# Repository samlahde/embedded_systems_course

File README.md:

# embedded_systems_course
Robotic car for embedded systems project course

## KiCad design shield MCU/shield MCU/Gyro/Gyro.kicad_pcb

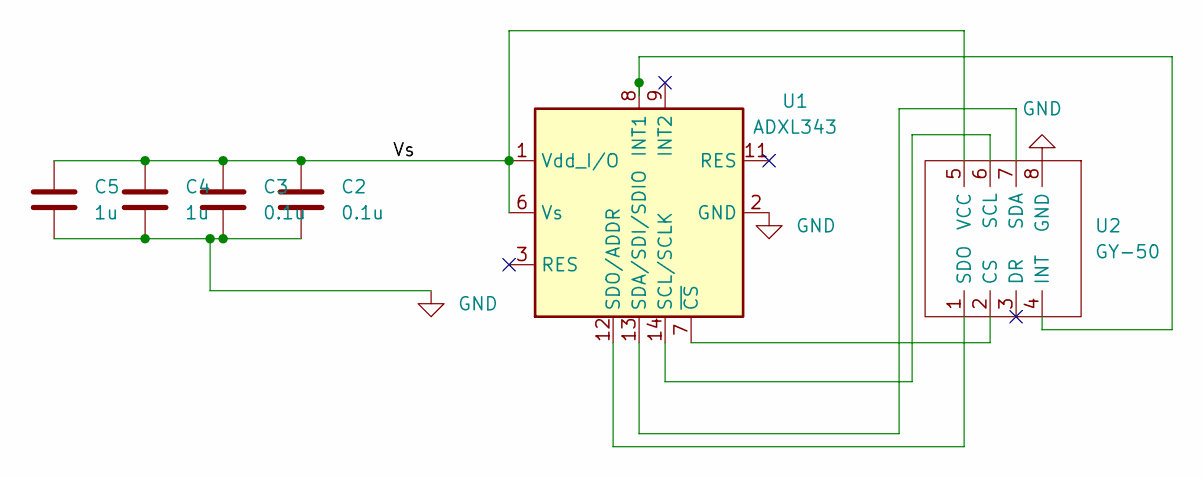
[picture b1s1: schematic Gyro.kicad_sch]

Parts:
C2, C3: 0.1u; C_1206_3216Metric
C4, C5: 1u; C_1206_3216Metric
U1: ADXL343; LGA-14_3x5mm_P0.8mm_LayoutBorder1x6y
U2: GY-50

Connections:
/Vs: C2.1, C3.1, C4.1, C5.1, U1.1 (Vdd_I/O), U1.6 (Vs), U2.5 (VCC)
GND: C2.2, C3.2, C4.2, C5.2, U1.2 (GND), U1.4 (GND), U1.5 (GND), U2.8 (GND)
unnamed: U1.7 (~CS), U2.2 (CS)
unnamed: U1.8 (INT1), U2.4 (INT)
unnamed: U1.12 (SDO/ADDR), U2.1 (SDO)
unnamed: U1.13 (SDA/SDI/SDIO), U2.7 (SDA)
unnamed: U1.14 (SCL/SCLK), U2.6 (SCL)

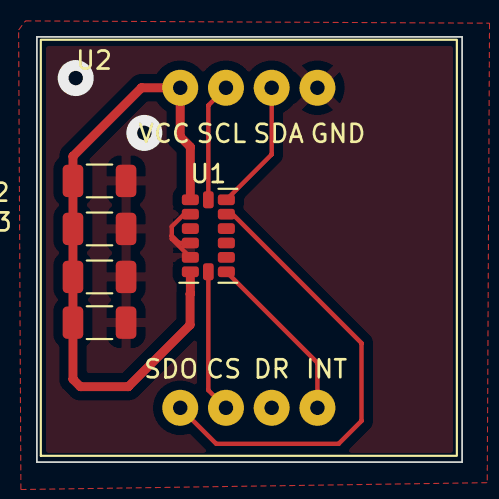
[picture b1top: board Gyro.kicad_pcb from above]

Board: 2 copper layers, 23.6 x 23.6 mm, 6 parts (0 on the bottom side), 7 nets.

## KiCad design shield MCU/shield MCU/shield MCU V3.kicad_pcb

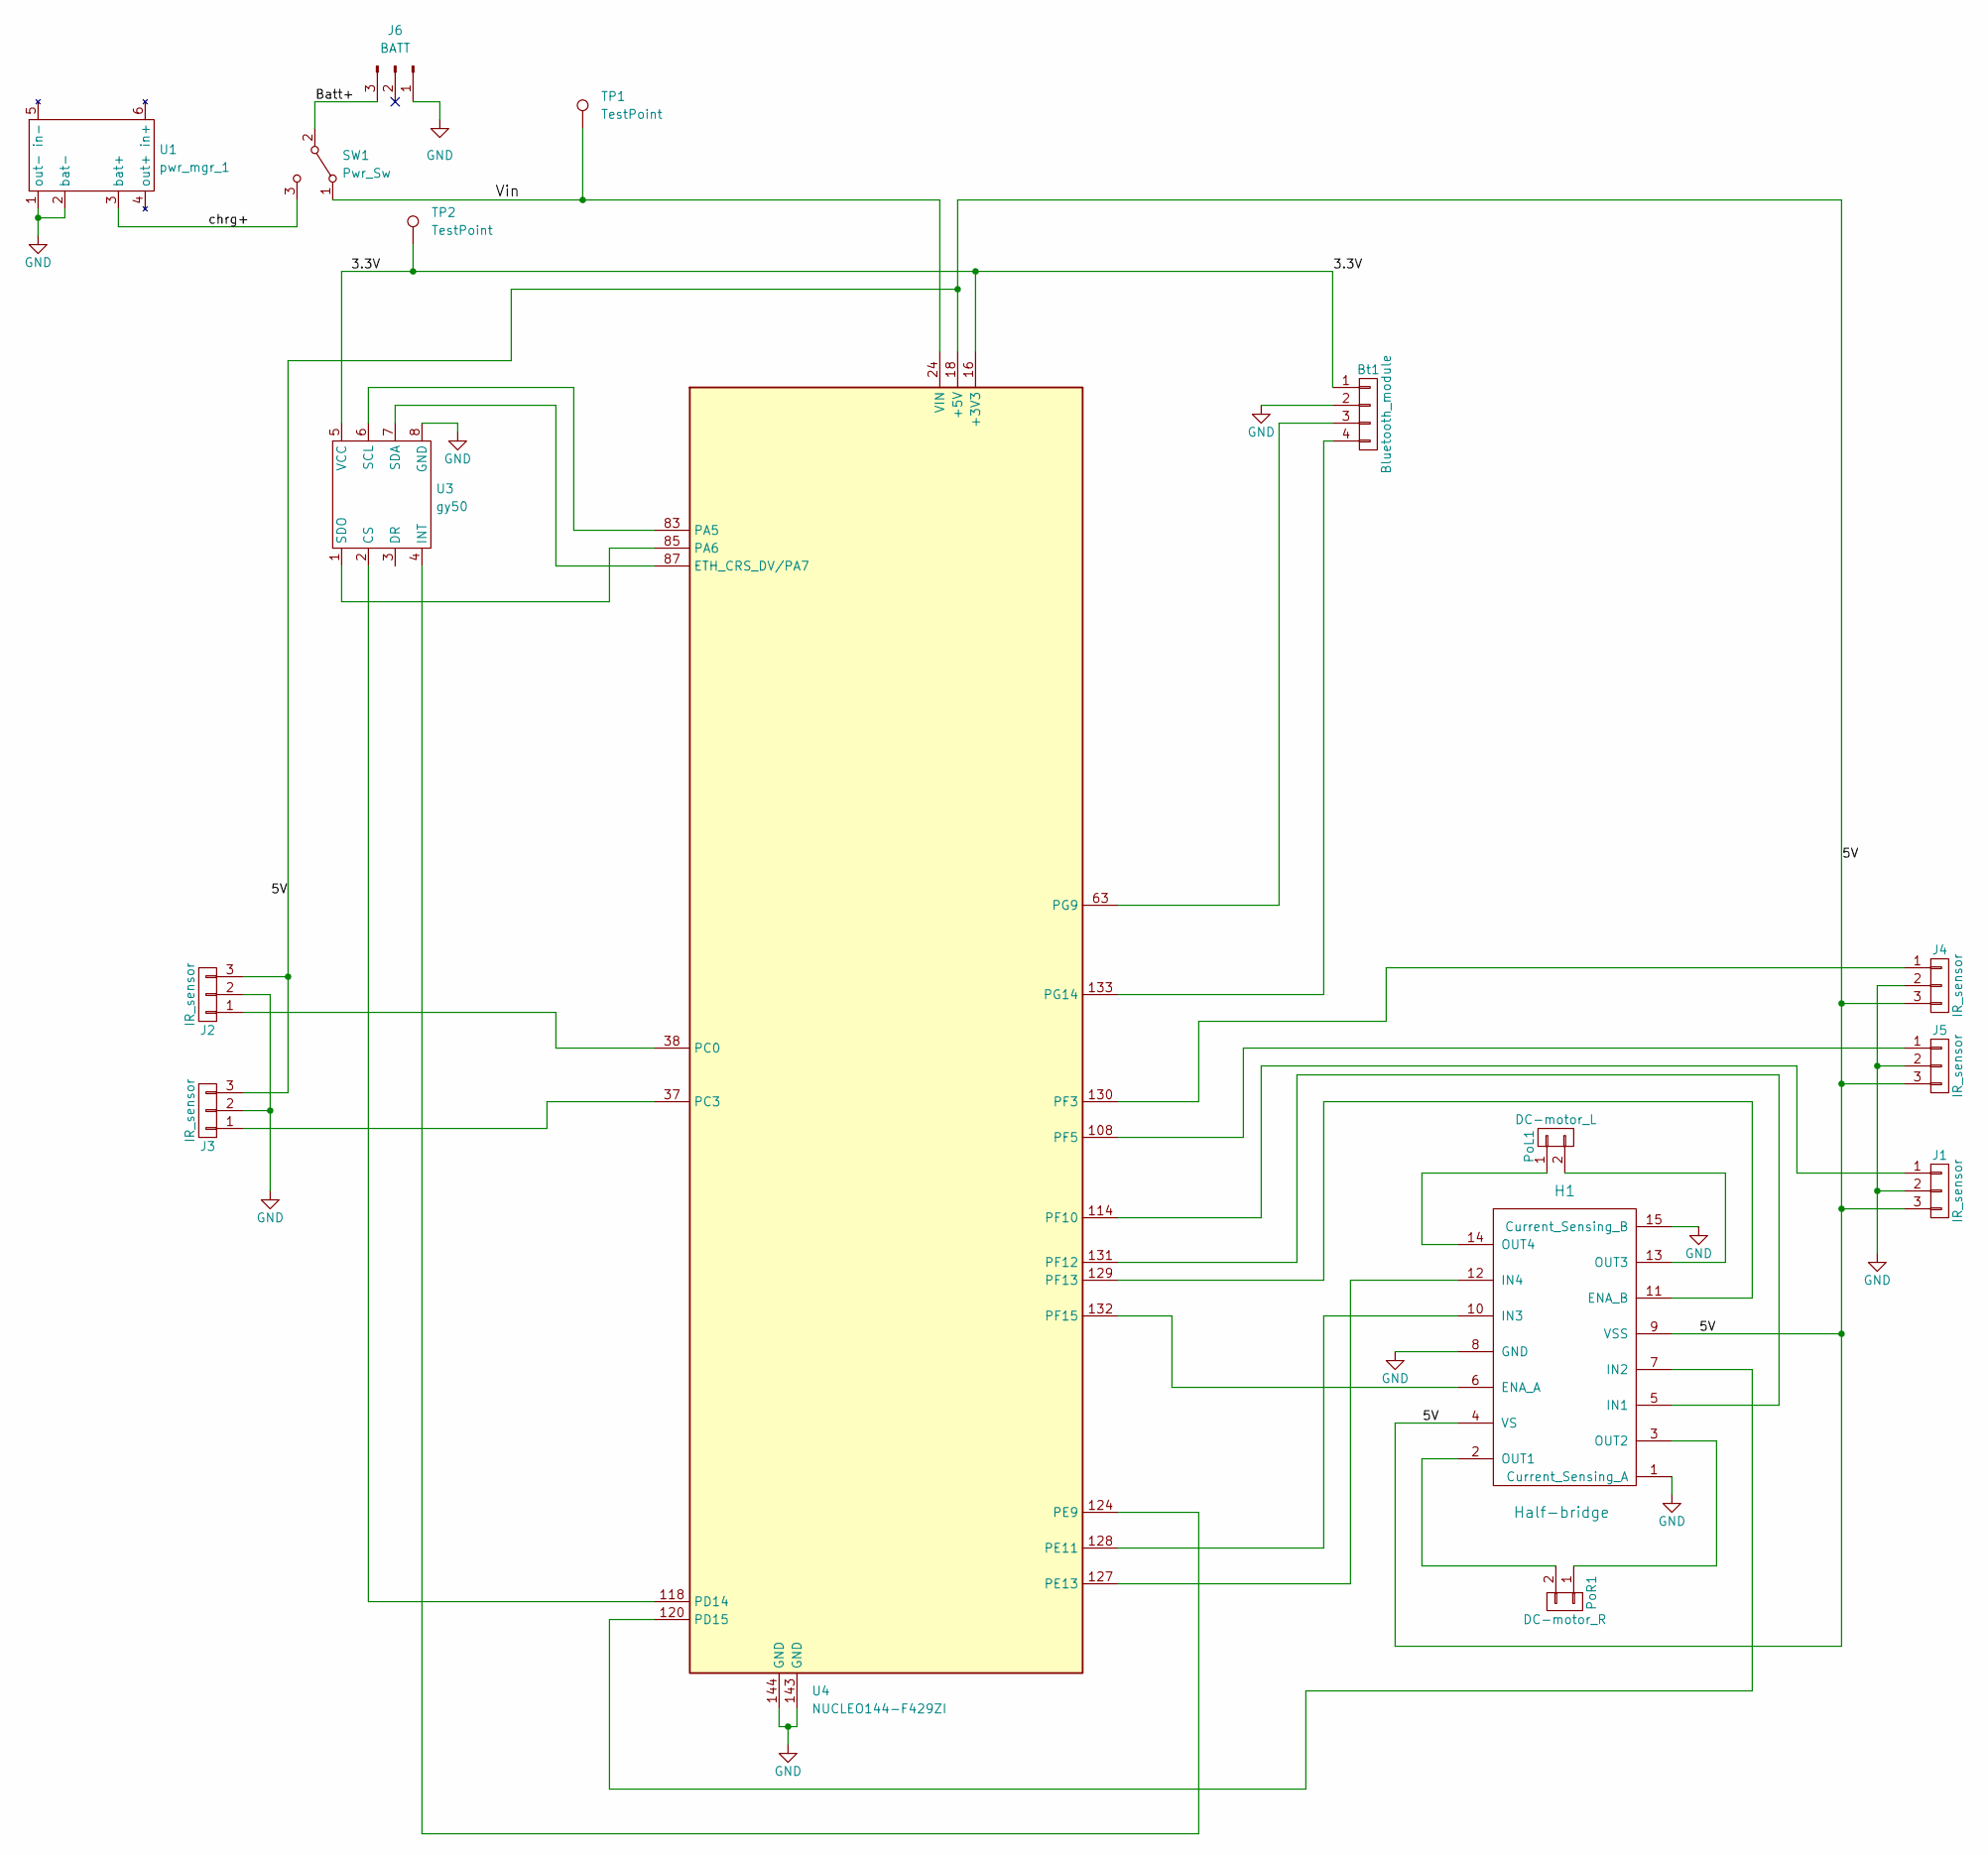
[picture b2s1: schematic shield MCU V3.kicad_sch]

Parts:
Bt1: Bluetooth_module; PinHeader_1x04_P2.54mm_Vertical
H1: Half-bridge; L298HN
J1, J2, J3, J4, J5: IR_sensor; PinHeader_1x03_P2.54mm_Vertical
J6: BATT; Connector_3pin
PoL1: DC-motor_L; PinHeader_1x02_P2.54mm_Horizontal
PoR1: DC-motor_R; PinHeader_1x02_P2.54mm_Horizontal
SW1: Pwr_Sw; SPDT
TP1, TP2: TestPoint; Pin_D0.7mm_L6.5mm_W1.8mm_FlatFork
U1: pwr_mgr_1; TPS4056
U3: gy50; GY-50
U4: NUCLEO144-F429ZI; ST_Morpho_Connector_144_STLink_MountingHoles_modded

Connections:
/3.3V: Bt1.1, TP2.1, U3.5 (VCC), U4.16 (+3V3)
/5V: H1.4 (VS), H1.9 (VSS), J1.3, J2.3, J3.3, J4.3, J5.3, U4.18 (+5V)
/Batt+: J6.3, SW1.2 (B)
/Vin: SW1.1 (A), TP1.1, U4.24 (VIN)
/chrg+: SW1.3 (C), U1.3 (bat+)
GND: Bt1.2, H1.1 (Current_Sensing_A), H1.8 (GND), H1.15 (Current_Sensing_B), J1.2, J2.2, J3.2, J4.2, J5.2, J6.1, U1.1 (out-), U1.2 (bat-), U3.8 (GND), U4.143 (GND), U4.144 (GND)
unnamed: Bt1.3, U4.63 (PG9)
unnamed: Bt1.4, U4.133 (PG14)
unnamed: H1.2 (OUT1), PoR1.2
unnamed: H1.3 (OUT2), PoR1.1
unnamed: H1.5 (IN1), U4.131 (PF12)
unnamed: H1.6 (ENA_A), U4.132 (PF15)
unnamed: H1.7 (IN2), U4.120 (PD15)
unnamed: H1.10 (IN3), U4.128 (PE11)
unnamed: H1.11 (ENA_B), U4.129 (PF13)
unnamed: H1.12 (IN4), U4.127 (PE13)
unnamed: H1.13 (OUT3), PoL1.2
unnamed: H1.14 (OUT4), PoL1.1
unnamed: J1.1, U4.114 (PF10)
unnamed: J2.1, U4.38 (PC0)
unnamed: J3.1, U4.37 (PC3)
unnamed: J4.1, U4.130 (PF3)
unnamed: J5.1, U4.108 (PF5)
unnamed: U3.1 (SDO), U4.85 (PA6)
unnamed: U3.2 (CS), U4.118 (PD14)
unnamed: U3.4 (INT), U4.124 (PE9)
unnamed: U3.6 (SCL), U4.83 (PA5)
unnamed: U3.7 (SDA), U4.87 (ETH_CRS_DV/PA7)

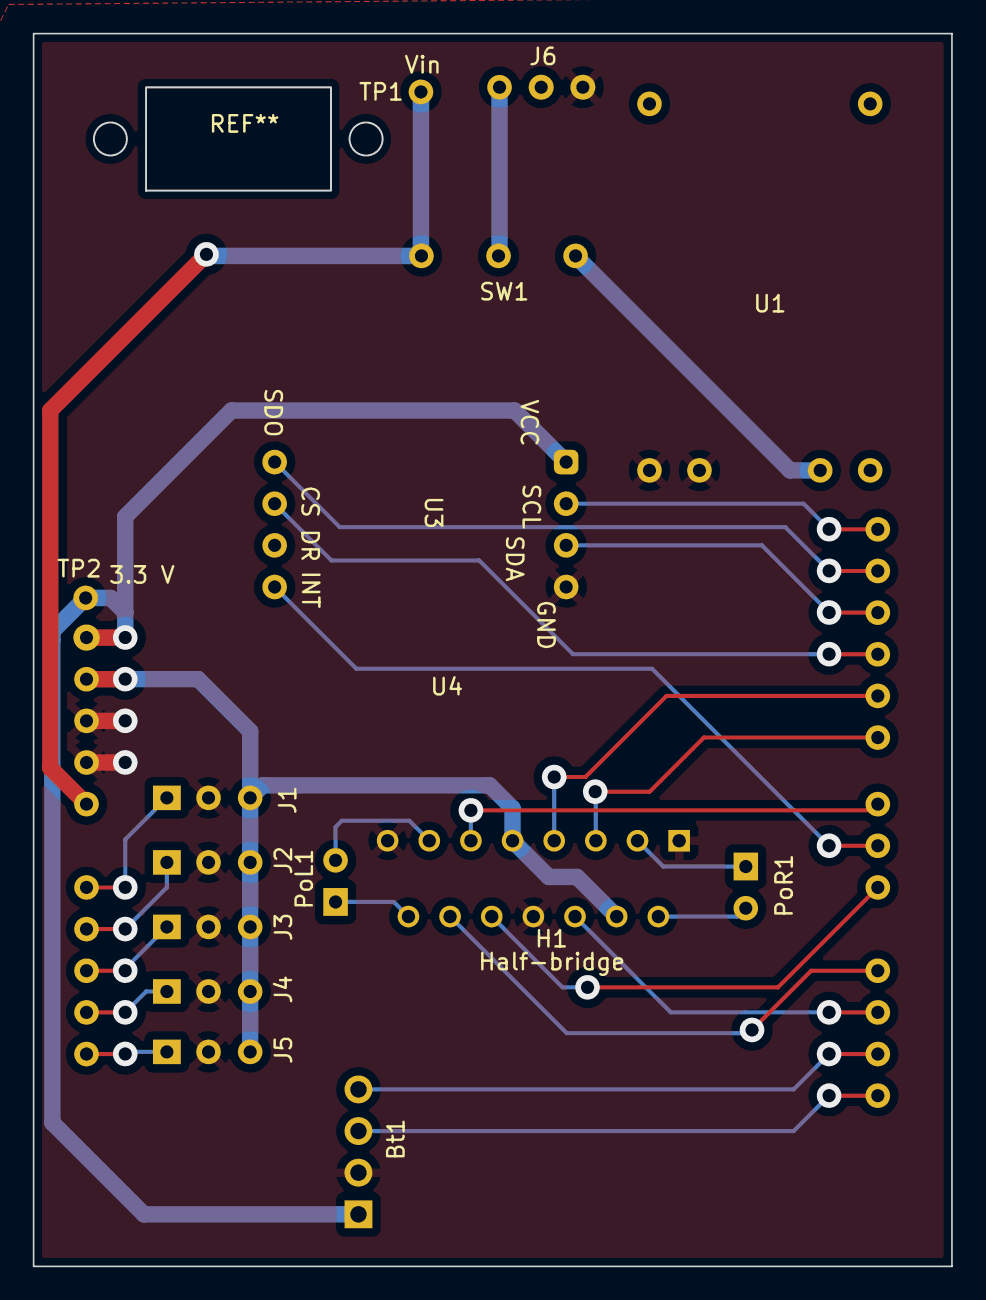
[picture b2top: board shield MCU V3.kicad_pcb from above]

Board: 2 copper layers, 56.0 x 75.2 mm, 16 parts (0 on the bottom side), 28 nets.

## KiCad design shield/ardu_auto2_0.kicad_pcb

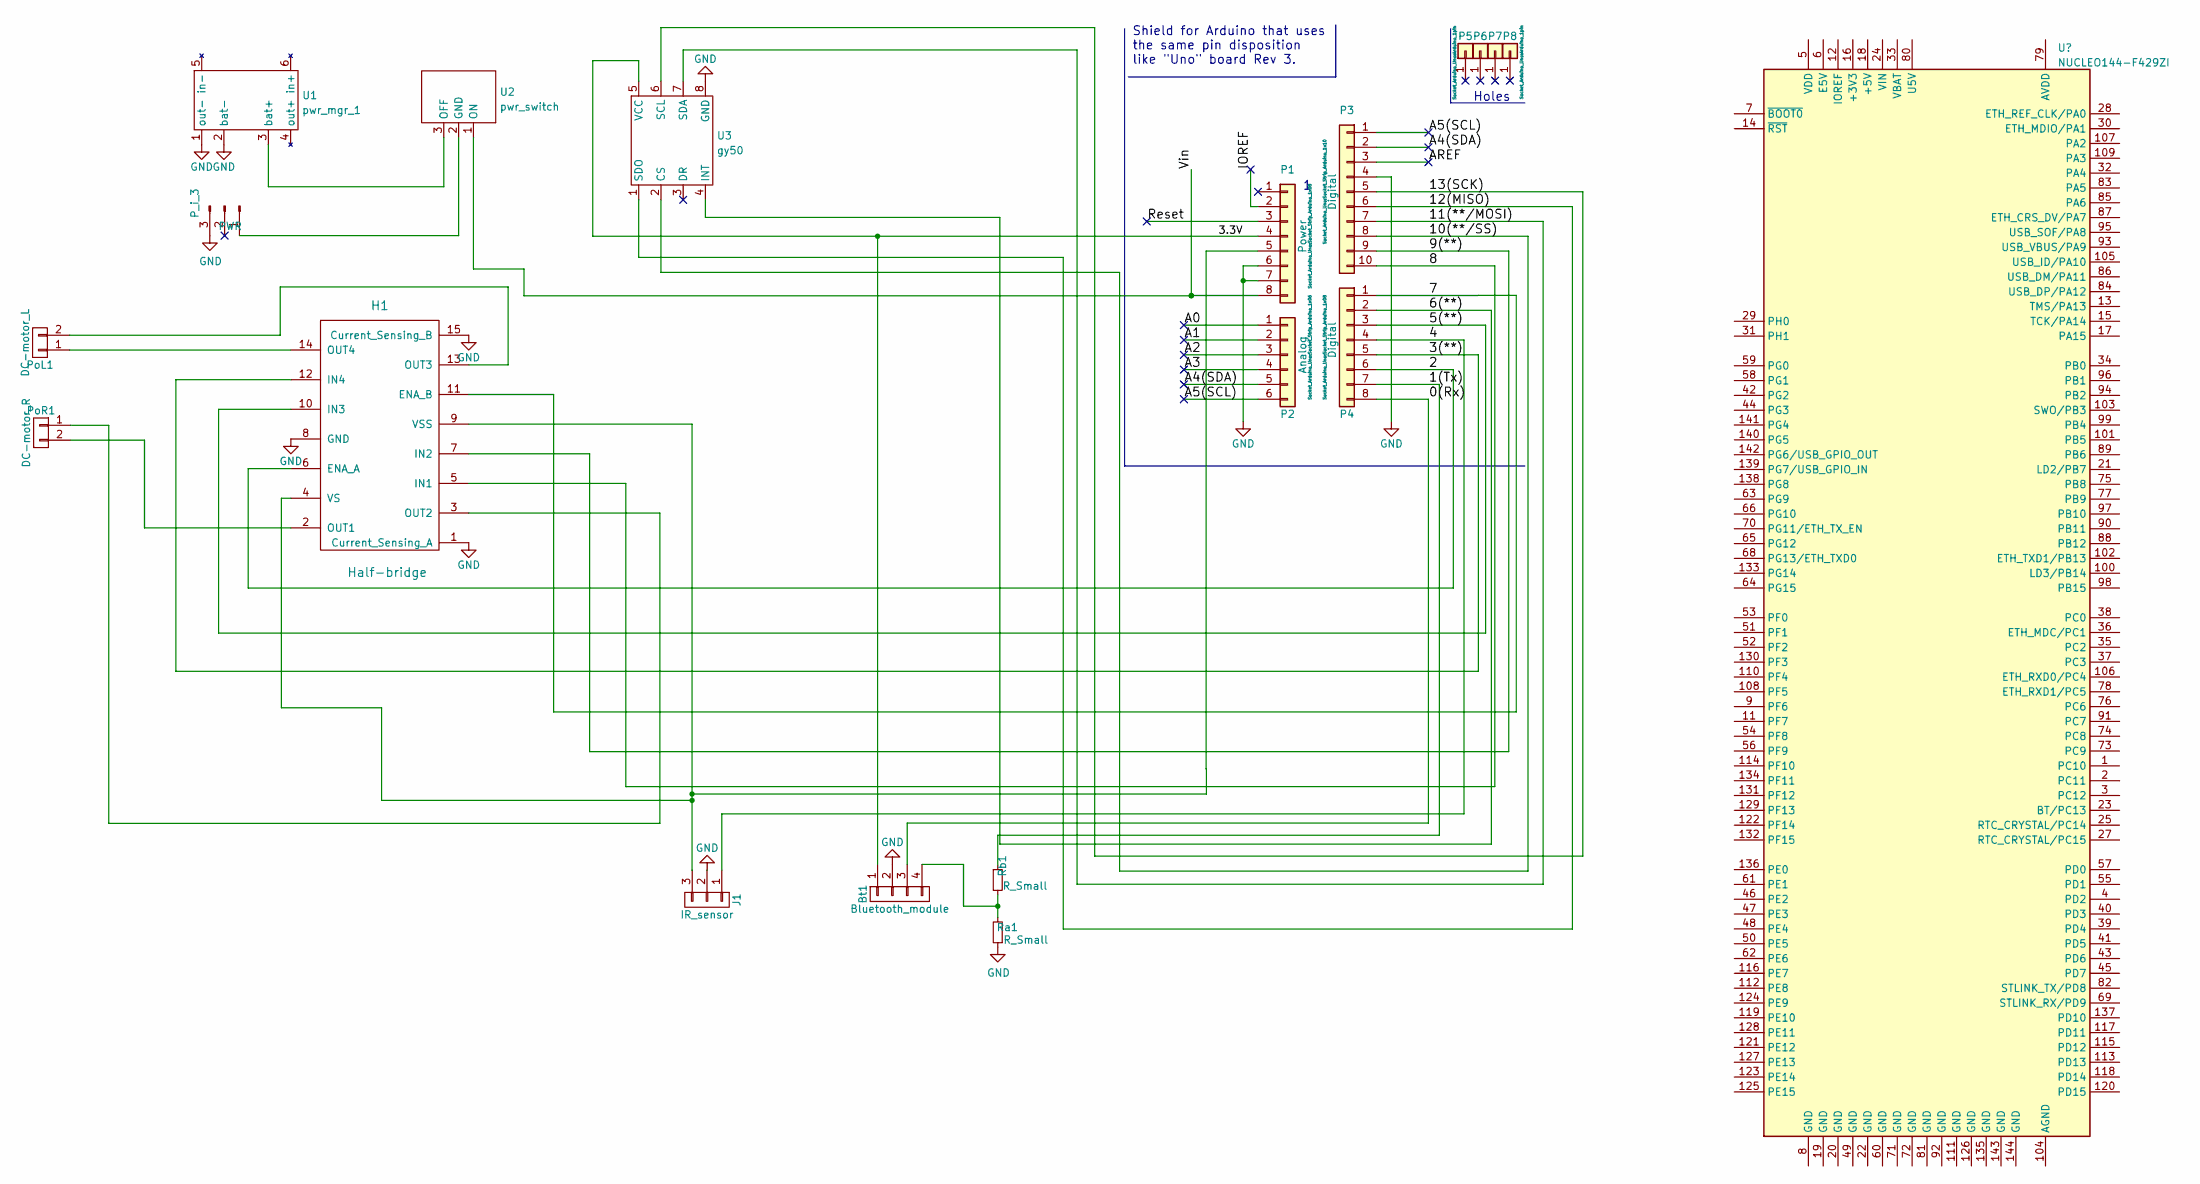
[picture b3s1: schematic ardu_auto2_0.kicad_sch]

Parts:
Bt1: Bluetooth_module; PinHeader_1x04_P2.54mm_Vertical
H1: Half-bridge
J1: IR_sensor; PinHeader_1x03_P2.54mm_Vertical
P1: Power; Socket_Strip_Arduino_1x08
P2: Analog; Socket_Strip_Arduino_1x06
P3: Digital; Socket_Strip_Arduino_1x10
P4: Digital; Socket_Strip_Arduino_1x08
P5, P6, P7, P8: CONN_01X01; Arduino_1pin
P_i_3: PWR; PinHeader_1x03_P2.54mm_Horizontal
PoL1: DC-motor_L; PinHeader_1x02_P2.54mm_Horizontal
PoR1: DC-motor_R; PinHeader_1x02_P2.54mm_Horizontal
Ra1: R_Small; PinHeader_1x02_P2.54mm_Horizontal
Rb1: R_Small; PinHeader_1x02_P2.54mm_Horizontal
U1: pwr_mgr_1; pwr_mfr_1
U2: pwr_switch; pwr_stw
U3: gy50

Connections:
/0(Rx): Bt1.3, P4.8
/1(Tx): P4.7, Rb1.1
/2: H1.6 (ENA_A), P4.6
/3(**): H1.12 (IN4), P4.5
/3.3V: Bt1.1, P1.4, U3.5 (VCC)
/4: J1.1, P4.4
/5(**): H1.10 (IN3), P4.3
/6(**): P4.2, U3.4 (INT)
/7: H1.11 (ENA_B), P4.1
/8: H1.5 (IN1), P3.10
/9(**): H1.7 (IN2), P3.9
/10(**/SS): P3.8, U3.2 (CS)
/11(**/MOSI): P3.7, U3.7 (SDA)
/12(MISO): P3.6, U3.1 (SDO)
/13(SCK): P3.5, U3.6 (SCL)
/A0: P2.1
/A1: P2.2
/A2: P2.3
/A3: P2.4
/A4(SDA): P2.5, P3.2
/A5(SCL): P2.6, P3.1
/AREF: P3.3
/IOREF: P1.2
/Reset: P1.3
/Vin: P1.8, U2.1 (ON)
GND: Bt1.2, H1.1 (Current_Sensing_A), H1.8 (GND), H1.15 (Current_Sensing_B), J1.2, P1.6, P1.7, P3.4, P_i_3.3, Ra1.1, U1.1 (out-), U1.2 (bat-), U3.8 (GND)
unnamed: Bt1.4, Ra1.2, Rb1.2
unnamed: H1.2 (OUT1), PoR1.2
unnamed: H1.3 (OUT2), PoR1.1
unnamed: H1.13 (OUT3), PoL1.2
unnamed: H1.14 (OUT4), PoL1.1
unnamed: H1.4 (VS), H1.9 (VSS), J1.3, P1.5
unnamed: P_i_3.1, U2.2 (GND)
unnamed: U1.3 (bat+), U2.3 (OFF)

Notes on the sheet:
Shield for Arduino that uses the same pin disposition like "Uno" board Rev 3.
Holes

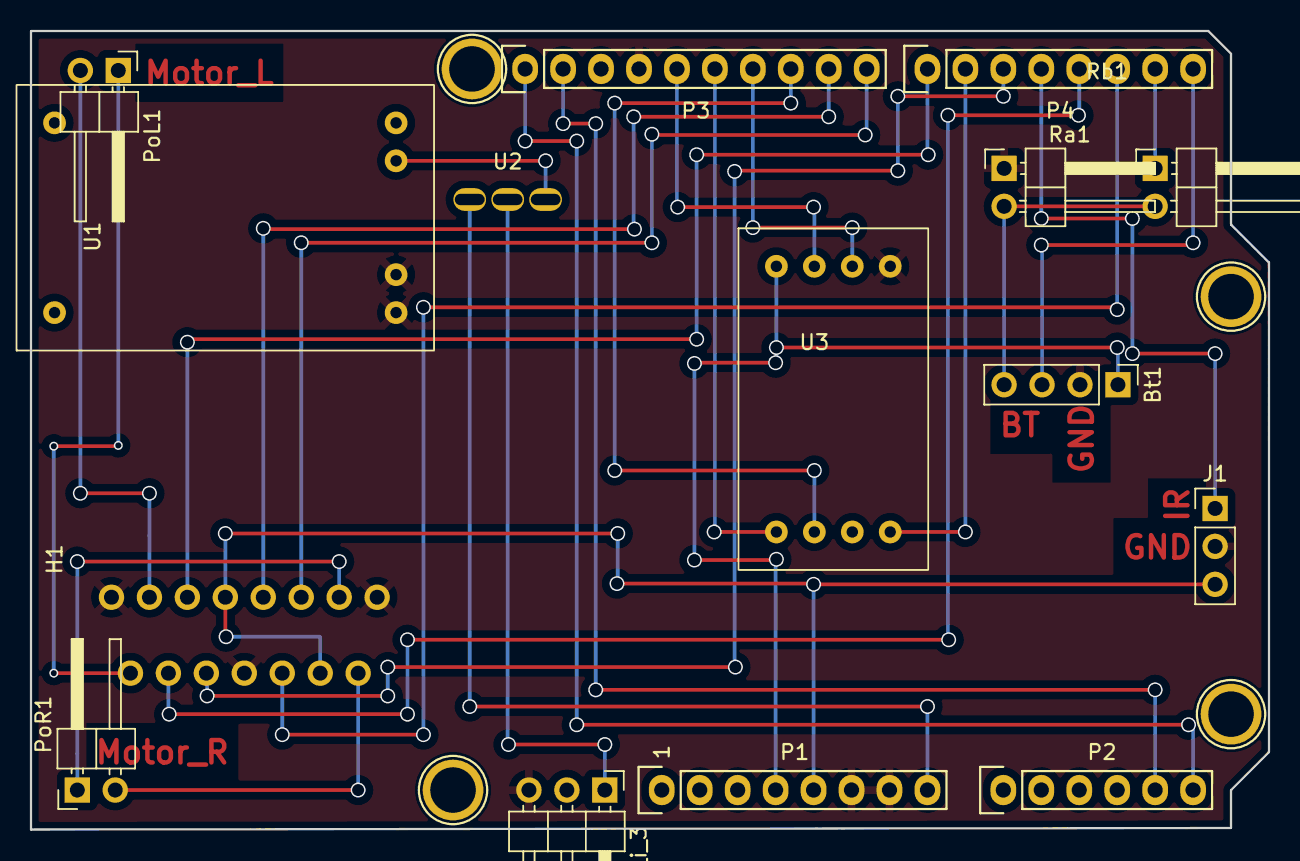
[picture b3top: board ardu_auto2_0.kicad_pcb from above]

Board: 2 copper layers, 82.9 x 53.4 mm, 19 parts (0 on the bottom side), 27 nets.

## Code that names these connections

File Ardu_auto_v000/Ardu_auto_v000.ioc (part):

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Mcu.Name=STM32F429ZITx
Mcu.Package=LQFP144
Mcu.UserName=STM32F429ZITx
PA13.Mode=Trace_Asynchronous_SW
PA13.Signal=SYS_JTMS-SWDIO
PA14.Mode=Trace_Asynchronous_SW
PA14.Signal=SYS_JTCK-SWCLK
PA2.Mode=Asynchronous
PA2.Signal=USART2_TX
PA3.Mode=Asynchronous
PA3.Signal=USART2_RX
PA5.GPIOParameters=GPIO_Label
PA5.GPIO_Label=SCK
PA5.Mode=Full_Duplex_Master
PA5.Signal=SPI1_SCK
PA6.GPIOParameters=GPIO_Label
PA6.GPIO_Label=SDO
PA6.Mode=Full_Duplex_Master
PA6.Signal=SPI1_MISO
PA7.GPIOParameters=GPIO_Label
PA7.GPIO_Label=SDA
PA7.Mode=Full_Duplex_Master
PA7.Signal=SPI1_MOSI
PB3.Mode=Trace_Asynchronous_SW
PB3.Signal=SYS_JTDO-SWO
PB8.Signal=I2C1_SCL
PB9.Signal=I2C1_SDA
PC0.GPIOParameters=GPIO_Label
PC0.GPIO_Label=IR5
PC0.Signal=ADCx_IN10
PC3.GPIOParameters=GPIO_Label
PC3.GPIO_Label=IR4
PC3.Signal=ADCx_IN13
PD14.GPIOParameters=PinState,GPIO_PuPd,GPIO_Label
PD14.GPIO_Label=SPI_CS
PD14.GPIO_PuPd=GPIO_PULLDOWN
PD14.PinState=GPIO_PIN_SET
PD14.Signal=GPIO_Output
PD15.GPIOParameters=PinState,GPIO_PuPd,GPIO_Label,GPIO_ModeDefaultOutputPP
PD15.GPIO_Label=IN2
PD15.GPIO_ModeDefaultOutputPP=GPIO_MODE_OUTPUT_PP
PD15.GPIO_PuPd=GPIO_PULLDOWN
PD15.PinState=GPIO_PIN_SET
PD15.Signal=GPIO_Output
PE11.GPIOParameters=PinState,GPIO_PuPd,GPIO_Label
PE11.GPIO_Label=IN3
PE11.GPIO_PuPd=GPIO_PULLDOWN
PE11.PinState=GPIO_PIN_SET
PE11.Signal=GPIO_Output
PE13.GPIOParameters=PinState,GPIO_PuPd,GPIO_Label
PE13.GPIO_Label=IN4
PE13.GPIO_PuPd=GPIO_PULLDOWN
PE13.PinState=GPIO_PIN_SET
PE13.Signal=GPIO_Output
PE9.GPIOParameters=PinState,GPIO_PuPd,GPIO_Label
PE9.GPIO_Label=SPI_INT
PE9.GPIO_PuPd=GPIO_PULLDOWN
PE9.PinState=GPIO_PIN_SET
PE9.Signal=GPIO_Output
PF10.GPIOParameters=GPIO_Label
PF10.GPIO_Label=IR1
PF10.Mode=IN8
PF10.Signal=ADC3_IN8
PF12.GPIOParameters=PinState,GPIO_PuPd,GPIO_Label
PF12.GPIO_Label=IN1
PF12.GPIO_PuPd=GPIO_PULLDOWN
PF12.PinState=GPIO_PIN_SET
PF12.Signal=GPIO_Output
PF13.GPIOParameters=GPIO_PuPd,GPIO_Label
PF13.GPIO_Label=ENB
PF13.GPIO_PuPd=GPIO_PULLDOWN
PF13.Signal=GPIO_Output
PF15.GPIOParameters=PinState,GPIO_PuPd,GPIO_Label
PF15.GPIO_Label=ENA
PF15.GPIO_PuPd=GPIO_PULLDOWN
PF15.PinState=GPIO_PIN_SET
PF15.Signal=GPIO_Output
PF3.GPIOParameters=GPIO_Label
PF3.GPIO_Label=IR3
PF3.Mode=IN9
PF3.Signal=ADC3_IN9
PF5.GPIOParameters=GPIO_Label
PF5.GPIO_Label=IR2
PF5.Mode=IN15
PF5.Signal=ADC3_IN15
PG14.GPIOParameters=GPIO_Label
PG14.GPIO_Label=BT_TX
PG14.Mode=Asynchronous
PG14.Signal=USART6_TX
PG9.GPIOParameters=GPIO_Label
PG9.GPIO_Label=BT_RX
PG9.Mode=Asynchronous
PG9.Signal=USART6_RX
RCC.HSE_VALUE=8000000
RCC.SYSCLKFreq_VALUE=50000000
RCC.SYSCLKSource=RCC_SYSCLKSOURCE_PLLCLK
RCC.SYSCLKSourceVirtual=RCC_SYSCLKSOURCE_PLLCLK
board=NUCLEO-F429ZI
boardIOC=true

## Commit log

2022-02-11 Document templates
    Added document templates to git
2022-03-01 Laturi skemat
    Lisätty kansio jossa kaikki laturin kicad tiedostot
2022-03-03 Shield template
    Shield template for further use. Replace Uno wires with nucleo
2022-03-03 Docs update
    Removed old docs and added report PDF, it will be updated during project
2022-03-04 Ei muutoksia
2022-03-08 shield mcu
2022-03-19 Code template
    Initialization code template for software developement
2022-03-20 shield MCU parannettu schema
2022-03-21 Valmis schema
2022-03-23 vetoja vaille valmis
    Poistin kaikki käyttämättömät pinnit, koska helpottaa layouttia
2022-03-23 PCB layout done
2022-03-24 Obsolete folder
    Deleted obsolete folder
2022-03-24 pcb V2 made
2022-03-25 uusi pcb
2022-03-25 Init 2
    Added functions and SPI
2022-03-27 PCB with gnd layer
2022-03-31 PCB päivitetty
    switchien VIA koot muutettu ja L298N footprint päivitetty
2022-04-01 uus pcb
2022-04-01 bug fix
    Gyro working, added functions
2022-04-02 bug fix
    Pin fix
2022-04-04 pcb V3
    kaikki vedot samalla puolella
2022-04-04 pcb V3 korjattu
    ground korjattu
2022-04-07 Initial draft for motor control
2022-04-07 pcb pieni päivitys
2022-04-08 Add bt command controller
2022-04-08 bug fix
2022-04-08 Add function to print actual mt pin values 4 debug
2022-04-09 Bug fix
    Added continuous driving to X, stopping to Y, little move forward to up and little reverse to down. Fixed cases,
2022-04-14 Major rework, add self driving draft
    -Moved command structure to new header file
    -Moved move command logic from motor_control to bt_control for increased modularity
    -Created a draft of autonomous driving functionality
2022-04-15 Draft: Mapping functionality
    TODO: Include FatFs, continue development
2022-04-22 Fix to self driving
2022-04-22 Oma gyro schematic ja layout tehty
2022-05-10 fixed gyro regs
2022-05-10 fix_gyro2
2022-05-10 Implement self driving functionality
2022-05-10 Add break
2022-05-10 Init cmd_holder
2022-05-10 Minor additions, code cleanup
2022-05-10 Change print freq
2022-05-10 Stop car when switching to manual
2022-05-19 Viimeisimmät pienet muutokset
2022-05-23 Viimeinen versio

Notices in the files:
parts and their libraries:
Copyright 2021 Accelerated Designs. All rights reserved.
